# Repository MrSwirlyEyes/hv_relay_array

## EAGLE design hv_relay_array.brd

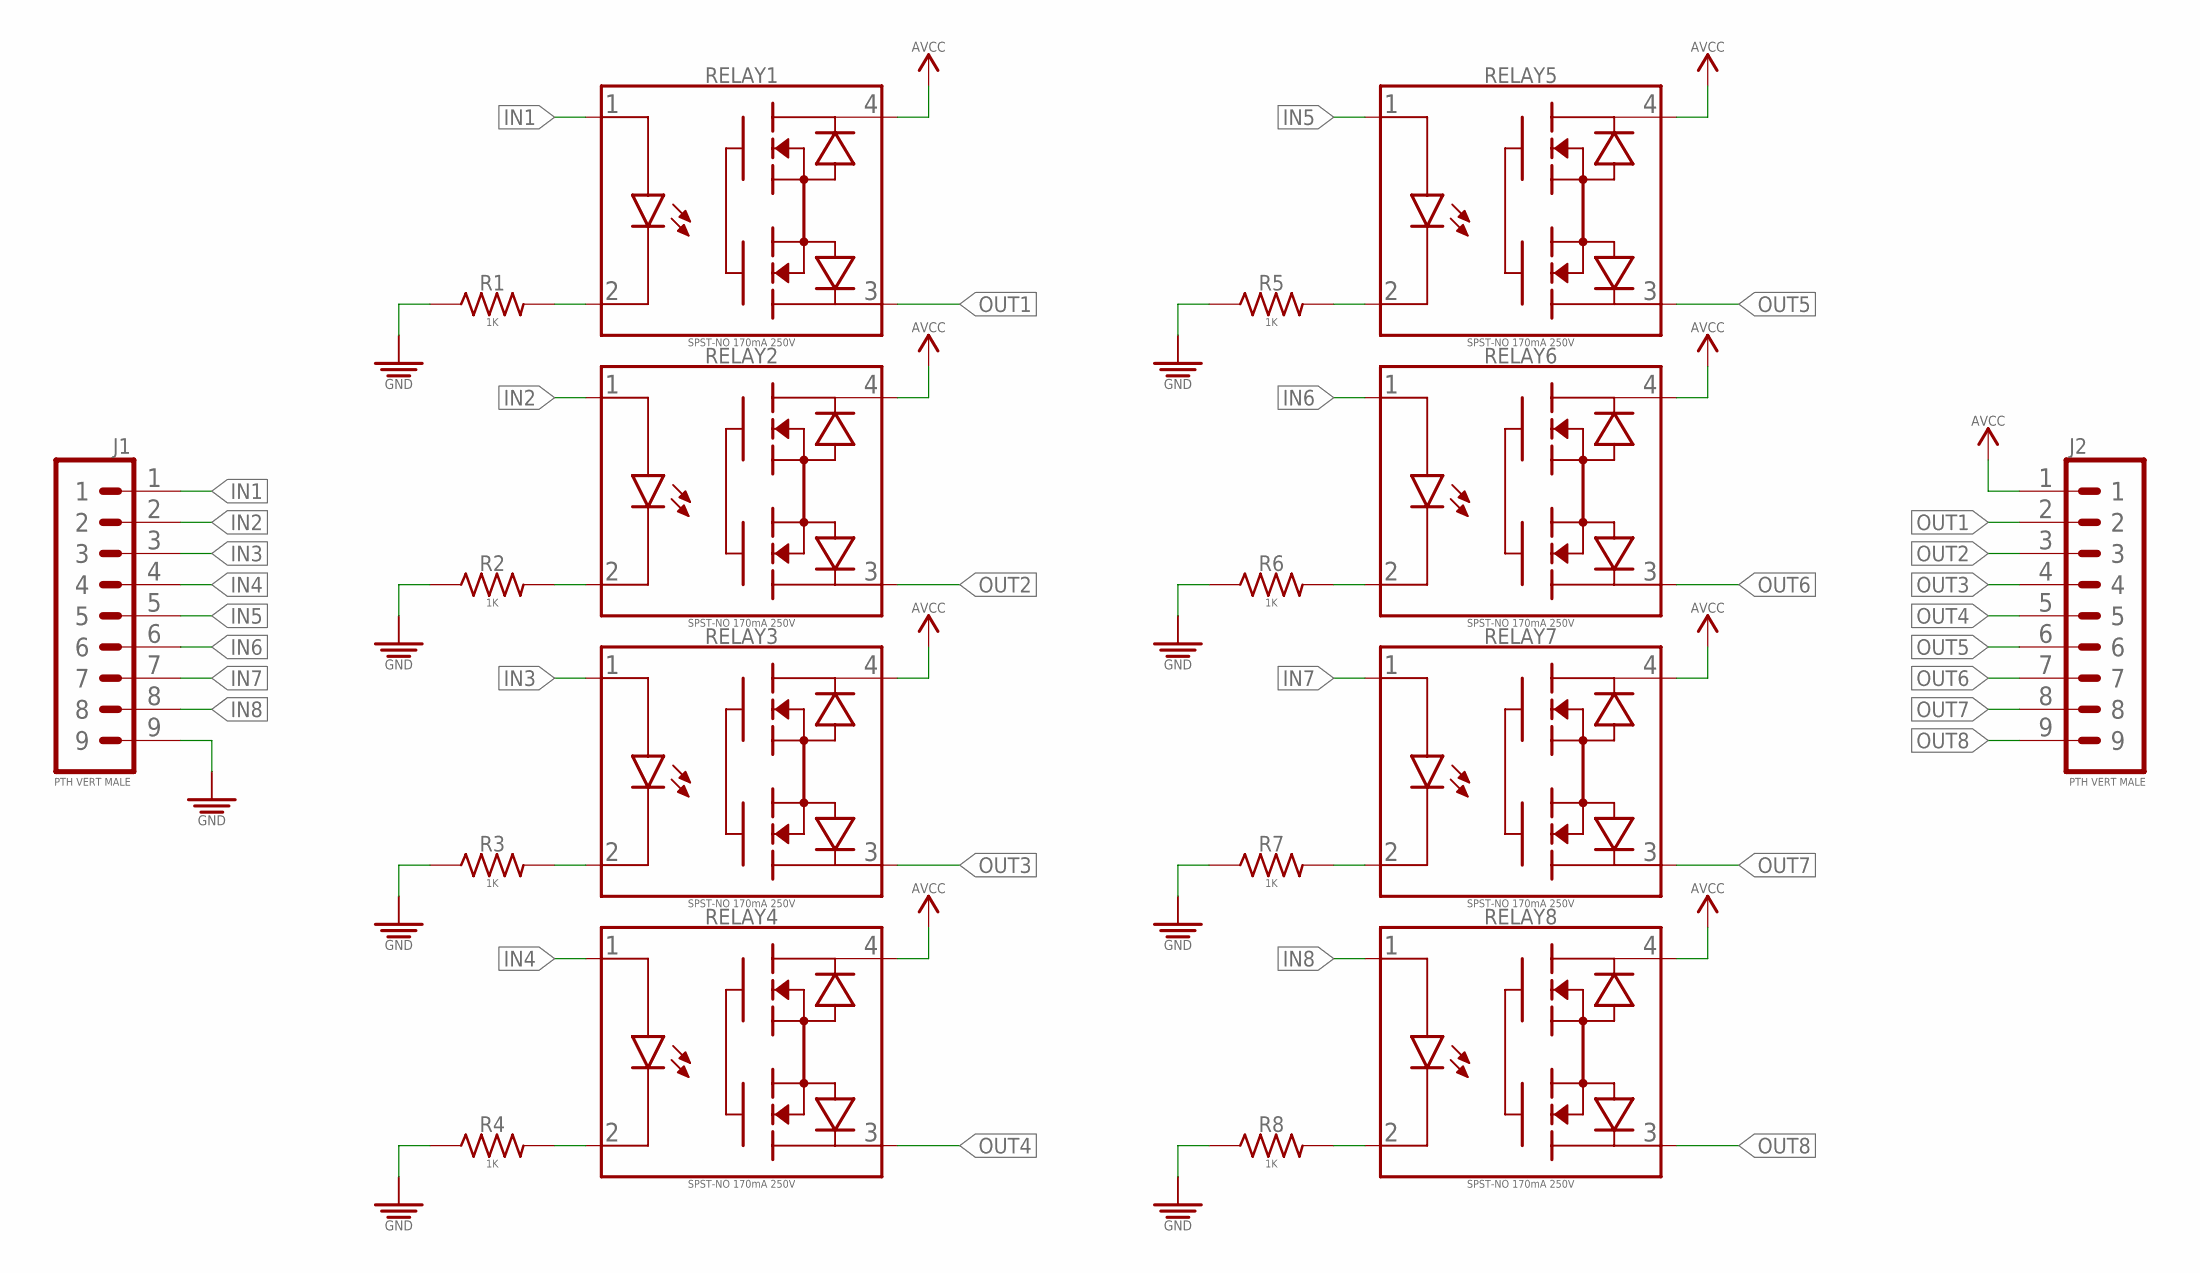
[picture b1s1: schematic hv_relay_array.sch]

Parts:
J1, J2: PTH VERT MALE; HDRV9W64P254_1X9_2286X254X838B
R1, R2, R3, R4, R5, R6, R7, R8: 1K; RESC1005X35_SMD-0402
RELAY1, RELAY2, RELAY3, RELAY4, RELAY5, RELAY6, RELAY7, RELAY8: SPST-NO 170mA 250V; SOP254P609X203-4

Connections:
AVCC: J2.1, RELAY1.4, RELAY2.4, RELAY3.4, RELAY4.4, RELAY5.4, RELAY6.4, RELAY7.4, RELAY8.4
GND: J1.9, R1.1, R2.1, R3.1, R4.1, R5.1, R6.1, R7.1, R8.1
IN1: J1.1, RELAY1.1
IN2: J1.2, RELAY2.1
IN3: J1.3, RELAY3.1
IN4: J1.4, RELAY4.1
IN5: J1.5, RELAY5.1
IN6: J1.6, RELAY6.1
IN7: J1.7, RELAY7.1
IN8: J1.8, RELAY8.1
unnamed: R1.2, RELAY1.2
unnamed: R2.2, RELAY2.2
unnamed: R3.2, RELAY3.2
unnamed: R4.2, RELAY4.2
unnamed: R5.2, RELAY5.2
unnamed: R6.2, RELAY6.2
unnamed: R7.2, RELAY7.2
unnamed: R8.2, RELAY8.2
OUT1: J2.2, RELAY1.3
OUT2: J2.3, RELAY2.3
OUT3: J2.4, RELAY3.3
OUT4: J2.5, RELAY4.3
OUT5: J2.6, RELAY5.3
OUT6: J2.7, RELAY6.3
OUT7: J2.8, RELAY7.3
OUT8: J2.9, RELAY8.3

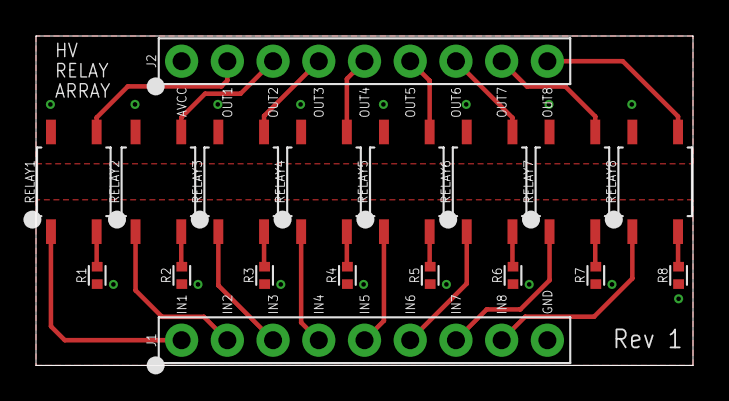
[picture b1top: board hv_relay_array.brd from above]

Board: 2 copper layers, 36.5 x 18.3 mm, 18 parts (0 on the bottom side), 26 nets.

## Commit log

2019-01-20 Initialize HV Relay Board repo.
